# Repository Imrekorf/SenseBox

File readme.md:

# Table of contents
- [Table of contents](#table-of-contents)
- [setup guide](#setup-guide)
- [Hardware setup guide](#hardware-setup-guide)
	- [Soldering list](#soldering-list)
	- [Managing the power source](#managing-the-power-source)
	- [Connecting the sensors](#connecting-the-sensors)
		- [Datasheets from the currently used sensors](#datasheets-from-the-currently-used-sensors)
		- [Schematics usage](#schematics-usage)
- [Programming the PCB](#programming-the-pcb)
- [Troubleshooting errors](#troubleshooting-errors)
	- [RTC](#rtc)
	- [SD](#sd)
	- [Sensor initialisation errors](#sensor-initialisation-errors)
- [Correct Installation check](#correct-installation-check)

# setup guide

1. Clone this github repo
2. Generate a MQTTSettings.dat file using the ArduinoConfig-Generator script.
3. Move generated MQTTSettings.dat to SD card's root folder.
4. Power the PCB.

# Hardware setup guide

## Soldering list
1. Solder the DC barreljack
2. Solder the BT1 Battery holder.[^1]
3. Solder the Laser dust sensor connector pins.[^1]
4. Solder the VR5V and VR5V jumpers.

[^1]: Currently the Laser Dust sensor connectors and Battery holder have not yet arrived so that sensor and battery holder can not be connected yet.

## Managing the power source
Depending on the circumstance you might want to power the PCB from the USB connection.<br>
To do this, **first**, you must make sure that VR5V and VR3V3 solder pads are not soldered. This can be identified by seeing 2 small pads on both the solder pads.<br>
Secondly you must solder the USB3V3 and USB5V to provide power to the board from the USB.<br>
If the DC barreljack is used you must **desolder** the USB3V3 and USB5V and then solder the VR3V3 and VR5V.<br>
<br>
To power the RTC you must either solder on the battery holder on the BT1 footprint. Or you can solder a wire from the VR3V3 or USB3V3, whichever is currently providing the 3V3 power, to the 3V3 pad of the Battery holder pads. See the board schematic included in the Schematics folder for more details.<br><br>

## Connecting the sensors
The sensors should be connected to the different JST headers provided on the board. To do this you need male `JST-PH 2.0 4 pin connectors`. 
These can be ordered from [vanallesenmeer.nl](https://www.vanallesenmeer.nl/JST-2.0-PH-4pin-set-recht-met-kabel-30cm) for €0.95.
These cables' other end can then be soldered to the sensors. Currently i2c compatible devices are wired as followed from left to right:
1. SCL : black
2. SDA : red
3. 3v3 : white
4. GND : yellow.

Other sensors' connection diagrams should be taken from the provided schematics.

### Datasheets from the currently used sensors
- [SCD30-datasheet](https://docs.rs-online.com/2d49/0900766b816b6f9d.pdf) & [SCD30-interface descriptor](https://docs.rs-online.com/ba78/0900766b816b6f9c.pdf)
- [Ambimate datasheet](https://docs.rs-online.com/6304/A700000006497831.pdf), [Product specifications](https://www.te.com/commerce/DocumentDelivery/DDEController?Action=srchrtrv&DocNm=108-133092&DocType=SS&DocLang=EN), [Application Specifications](https://www.te.com/commerce/DocumentDelivery/DDEController?Action=showdoc&DocId=Specification+Or+Standard%7F114-133092%7FB%7Fpdf%7FEnglish%7FENG_SS_114-133092_B.pdf%7FN-A), [customer drawings](https://eu.mouser.com/datasheet/2/418/7/ENG_CD_2314291_A2-2032749.pdf)
- [TSL2591](https://learn.adafruit.com/adafruit-tsl2591/downloads)
- [AS7262](https://learn.adafruit.com/adafruit-as7262-6-channel-visible-light-sensor/overview)
- [SM-UART-04L](https://www.farnell.com/datasheets/2756490.pdf)
- [MIX8410](https://wiki.seeedstudio.com/Grove-Gas_Sensor-O2-MIX8410/)
- [MAX4466](https://datasheets.maximintegrated.com/en/ds/MAX4465-MAX4469.pdf)
- [PCF8563](https://www.nxp.com/docs/en/data-sheet/PCF8563.pdf)

Any other datasheets needed are included in the EAGLE library. Check the description of the different components to find these datasheets.

### Schematics usage
The .sch and .brd file contain the electrical diagrams and PCB board layout respectively. The pdf contains a quick summary of the .sch file.
The .sch and .brd files can be loaded into the Autocad EAGLE software to make changes and view other information.
The .csv files contain JLCPCB part numbers and placements. These are used to order the right SMD components on the board.

# Programming the PCB
To program the ESP32 on the PCB, provide a power source, either through the USB or the barrel jack depending on the currently soldered connections.
Then load the code into the arduino ide by opening the .ino file. You then need to select the ESP32 dev module as your board in the Tools section.
If this is not already present follow the following [tutorial](https://randomnerdtutorials.com/installing-the-esp32-board-in-arduino-ide-windows-instructions/) to add support for these boards.
Select the correct port in the arduino ide and upload the code.
**important:** when the "connecting ...." prompt comes up, press and hold the RST and BOOT buttons, then release the RST button. if the prompt stops printing `.` or `-`'s then release the BOOT button.

# Troubleshooting errors
The most common errors in the serial output will be that either the RTC, SD or other sensors are not connected. Currently the program does not stop at these errors which could lead to a SYS_RST error message from the ESP32.
## RTC
If the RTC is not working there is either a short circuit on the i2c bus or the RTC does not have power. The RTC is the first module to be initialized in the system for logging purposes, so this has some major consequences when it's not working.

## SD
The most common SD card error is that it is not plugged in. Which can be solved by plugging in the SD card, or replugging the SD card and restarting the system when it was plugged in.
The provided SD card should be flashed with an FAT32 format to make sure the ESP32 can write to it.

## Sensor initialisation errors
If problems arise with the sensors not initializing it is likely due to bad wiring or not being connected at all.

# Correct Installation check
If the installation and connections are all correct you should see the following popping up in the serial monitor after a reset.

```
[14:39:31] [Info]: AmbiMate Firmware version 2.8
[14:39:32] [Info]: AS7262 initialized
[14:39:32] [Info]: SM_UART_4L found and initialized.
[14:39:32] [Info]: SCD30 initialized.
[14:39:32] [Info]: Found a TSL2591 sensor
[14:39:32] [Info]: TSL2591 bootup
------------------------------------
Gain:         25x (Medium)
Timing:       300 ms
------------------------------------

[14:39:33] [Info]: Connecting to WiFi .......
Connencted to wiFi with ip: 192.168.178.53
[14:39:38] [Info]: 
Starting connection to server...
[14:39:38] [Info]: The client SenseBox_test connects to the public mqtt broker
[54:39:40] [Info]: Mqtt broker connected
```

Followed by Info logs containing sensor data.
This data should also be partially tracable to the IoT platform.

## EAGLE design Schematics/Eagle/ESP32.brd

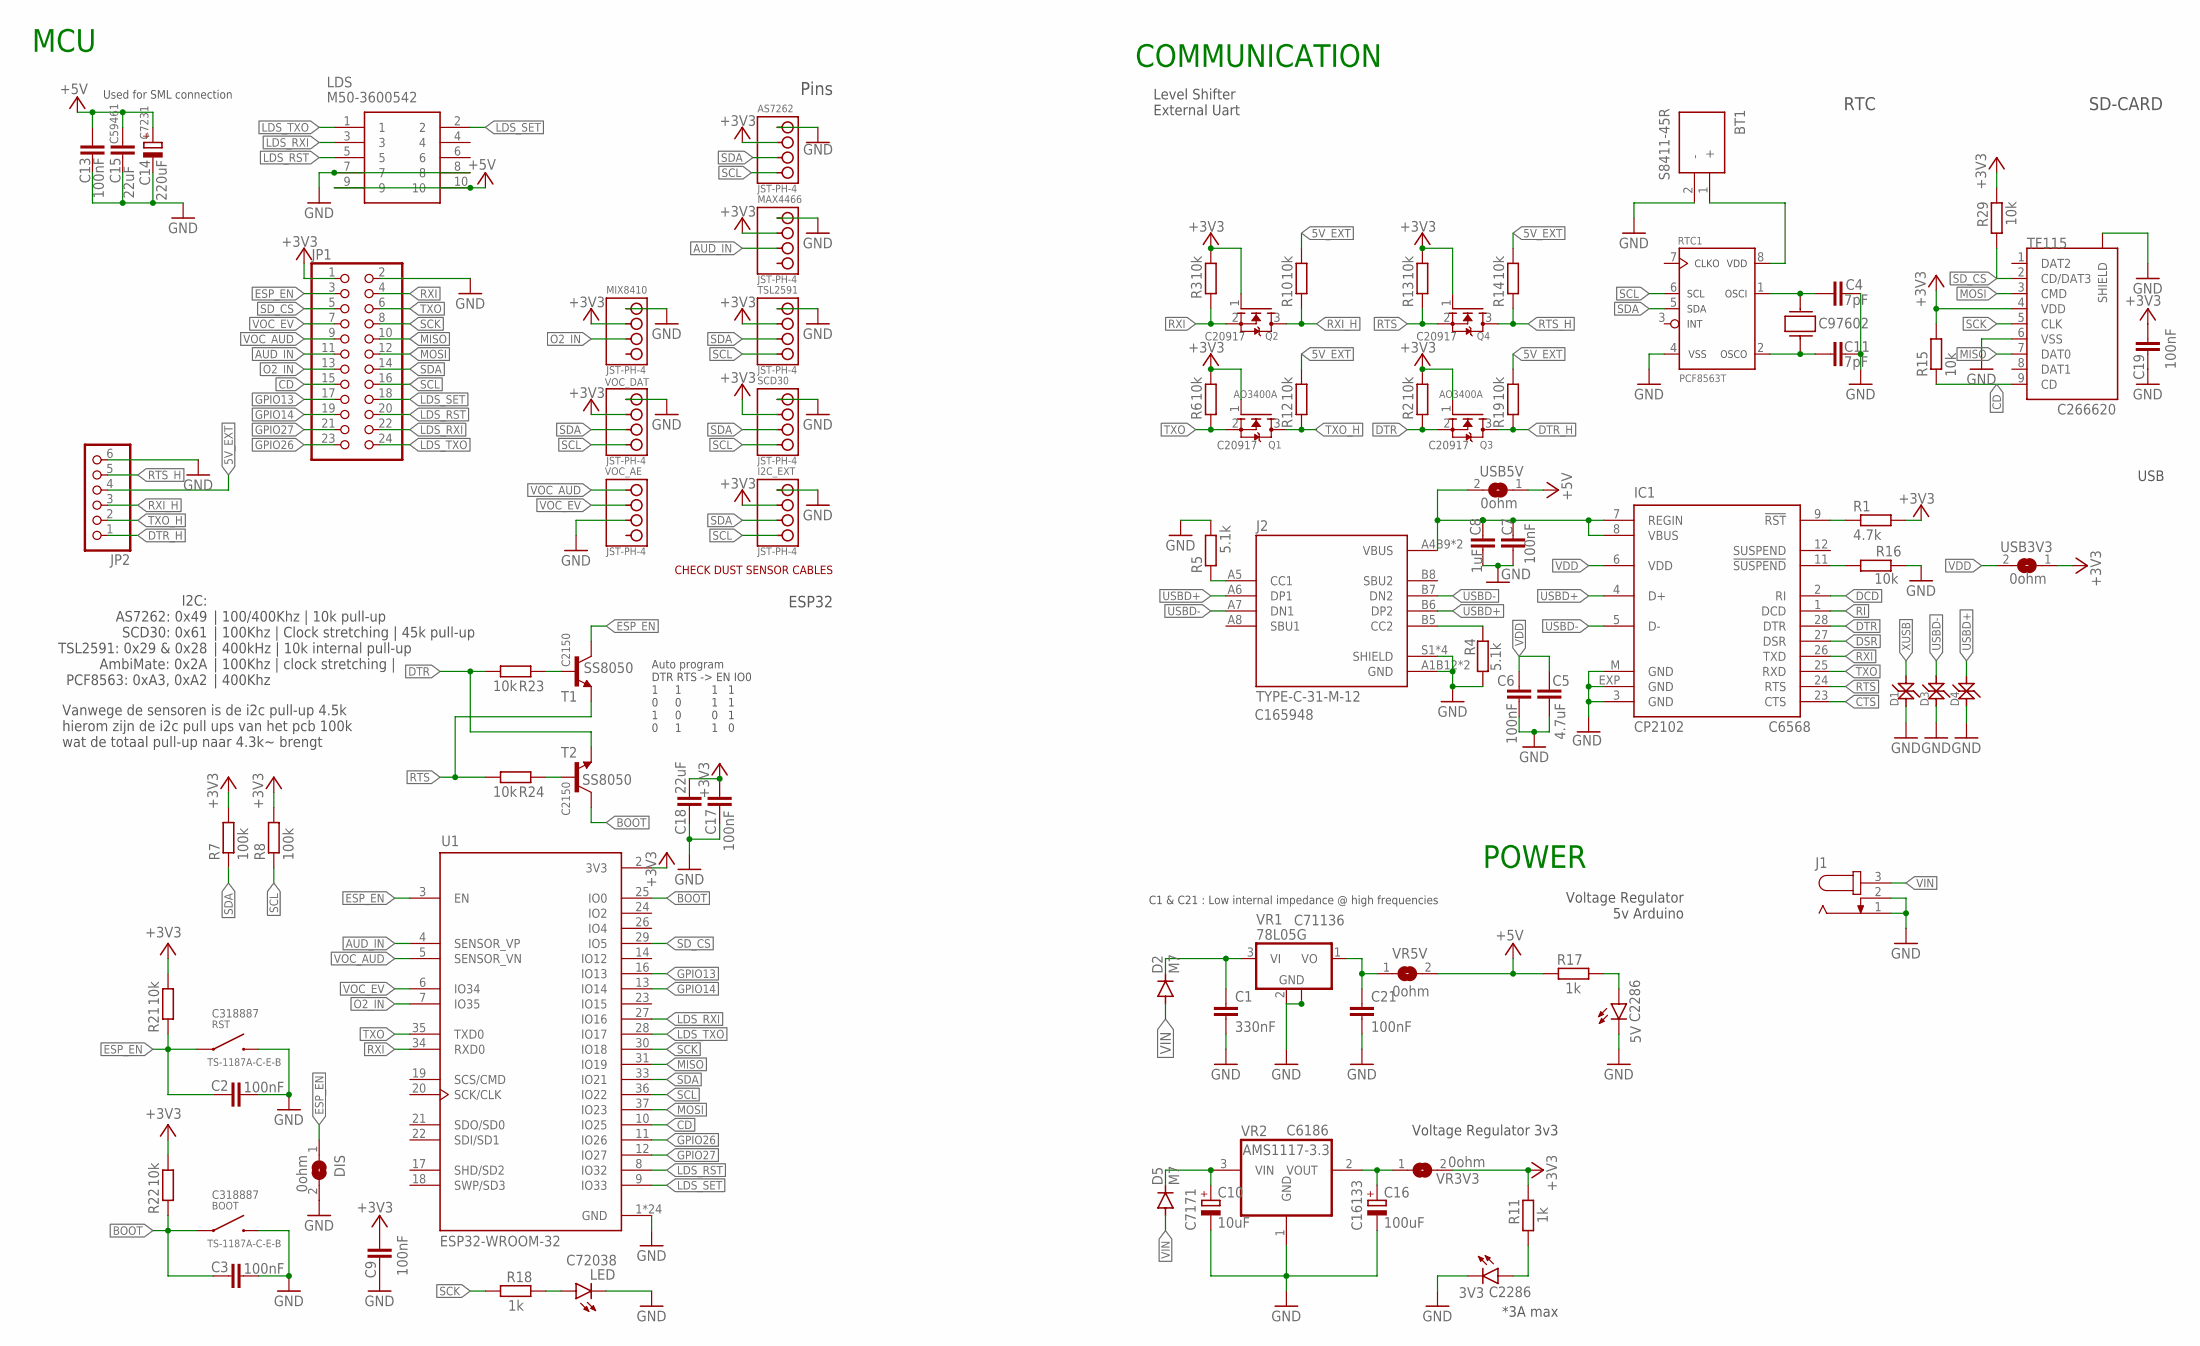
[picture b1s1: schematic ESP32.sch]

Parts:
3V3, 5V: C2286; CHIPLED_0603
AS7262: JST-PH-4
BOOT: TS-1187A-C-E-B
BT1: S8411-45R; S8411-45R_1
C1: 330nF; C0805
C2, C3, C6, C7, C9, C13, C17, C19, C21: 100nF; C0402
C4, C11: 7pF; C0402
C5: 4.7uF; C0402
C8: 1uF; C0402
C10: 10uF; A/3216-18R
C14: 220uF; D/7343-31R
C15, C18: 22uF; C0603
C16: 100uF; B/3528-21W
D1, D3, D4: LESD5D5.0CT1G
D2, D5: M7; DO-214AC
DIS: 0ohm; SJ
G1: 32.768KHZ
I2C_EXT: JST-PH-4
IC1: CP2102; MLP28
J1: JACK-PLUG1; SPC4078
J2: TYPE-C-31-M-12; HRO_TYPE-C-31-M-12
JP1: PINHD-2X12; 2X12
JP2: PINHD-1X6/90; 1X06/90
LDS: M50-3600542; M503600542
LED: YELLOW; CHIPLED_0603
MAX4466: JST-PH-4
MIX8410: JST-PH-4
Q1, Q2, Q3, Q4: AO3400A; SOT23
R1: 4.7k; R0402
R2, R3, R6, R10, R12, R13, R14, R15, R16, R19, R21, R22, R23, R24, R29: 10k; R0402
R4, R5: 5.1k; R0402
R7, R8: 100k; R0402
R11, R17, R18: 1k; R0805
RST: TS-1187A-C-E-B
RTC1: PCF8563T; SOIC8
SCD30: JST-PH-4
T1, T2: SS8050; SOT23-BEC
TF115: TF-115
TSL2591: JST-PH-4
U1: ESP32-WROOM-32; MODULE_ESP32-WROOM-32
USB3V3, USB5V: 0ohm; SJ
VOC_AE: JST-PH-4
VOC_DAT: JST-PH-4
VR1: 78L05G; SOT89
VR2: AMS1117-3.3; SOT223
VR3V3, VR5V: 0ohm; SJ

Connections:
5V_EXT: JP2.4, R10.1, R12.1, R14.1, R19.1
+3V3: AS7262.P2 (2), C9.2, C17.2, C18.2, C19.2, I2C_EXT.P2 (2), JP1.1, MAX4466.P2 (2), MIX8410.P2 (2), Q1.1 (G), Q2.1 (G), Q3.1 (G), Q4.1 (G), R1.2, R2.1, R3.1, R6.1, R7.2, R8.2, R11.2, R13.1, R15.2, R21.1, R22.1, R29.2, SCD30.P2 (2), TF115.4 (VDD), TSL2591.P2 (2), U1.2 (3V3), USB3V3.1, VOC_DAT.P2 (2), VR3V3.2
+5V: C13.1, C14.+, C15.1, LDS.9, LDS.10, R17.2, USB5V.1, VR5V.2
AUD_IN: JP1.11, MAX4466.P3 (3), U1.4 (SENSOR_VP)
BOOT: BOOT.A, BOOT.B (A), C3.1, R22.2, T2.C, U1.25 (IO0)
CD: JP1.15, R15.1, TF115.9 (CD), U1.10 (IO25)
CTS: IC1.23 (CTS)
DCD: IC1.2 (RI)
DSR: IC1.27 (DSR)
DTR: IC1.28 (DTR), Q3.2 (S), R2.2, R23.1, T2.E
DTR_H: JP2.1, Q3.3 (D), R19.2
ESP_EN: C2.1, DIS.1, JP1.3, R21.2, RST.A, RST.B (A), T1.C, U1.3 (EN)
GND: 3V3.C, 5V.C, AS7262.P1 (1), BOOT.C, BOOT.D (C), BT1.2 (-), C1.2, C2.2, C3.2, C4.2, C5.2, C6.2, C7.2, C8.2, C9.1, C10.-, C11.2, C13.2, C14.-, C15.2, C16.-, C17.1, C18.1, C19.1, C21.2, D1.P$1, D3.P$1, D4.P$1, DIS.2, I2C_EXT.P1 (1), IC1.3 (GND), IC1.EXP (GND), IC1.M (GND), J1.1, J1.2, J2.A1B12 (GND), J2.B1A12 (GND), J2.S1 (SHIELD), J2.S2 (SHIELD), J2.S3 (SHIELD), J2.S4 (SHIELD), JP1.2, JP2.6, LDS.7, LDS.8, LED.C, MAX4466.P1 (1), MIX8410.P1 (1), R4.2, R5.2, R16.1, RST.C, RST.D (C), RTC1.4 (VSS), SCD30.P1 (1), TF115.6 (VSS), TF115.10 (SHIELD), TF115.11 (SHIELD), TF115.12 (SHIELD), TF115.13 (SHIELD), TSL2591.P1 (1), U1.1 (GND), U1.15 (GND), U1.38 (GND), U1.39_1 (GND), U1.39_2 (GND), U1.39_3 (GND), U1.39_4 (GND), U1.39_5 (GND), U1.39_6 (GND), U1.39_7 (GND), U1.39_8 (GND), U1.39_9 (GND), U1.39_10 (GND), U1.39_11 (GND), U1.39_12 (GND), U1.39_13 (GND), U1.39_14 (GND), U1.39_15 (GND), U1.39_16 (GND), U1.39_17 (GND), U1.39_18 (GND), U1.39_19 (GND), U1.39_20 (GND), U1.39_21 (GND), VOC_AE.P3 (3), VOC_DAT.P1 (1), VR1.2 (GND), VR1.2@1 (GND), VR2.1 (GND)
GPIO13: JP1.17, U1.16 (IO13)
GPIO14: JP1.19, U1.13 (IO14)
GPIO26: JP1.23, U1.11 (IO26)
GPIO27: JP1.21, U1.12 (IO27)
LDS_RST: JP1.20, LDS.5, U1.8 (IO32)
LDS_RXI: JP1.22, LDS.3, U1.27 (IO16)
LDS_SET: JP1.18, LDS.2, U1.9 (IO33)
LDS_TXO: JP1.24, LDS.1, U1.28 (IO17)
MISO: JP1.10, TF115.7 (DAT0), U1.31 (IO19)
MOSI: JP1.12, TF115.3 (CMD), U1.37 (IO23)
unnamed: C4.1, G1.2, RTC1.1 (OSCI)
unnamed: R23.2, T1.B
unnamed: BT1.1 (+), RTC1.8 (VDD)
unnamed: 3V3.A, R11.1
unnamed: IC1.9 (!RST), R1.1
unnamed: C11.1, G1.1, RTC1.2 (OSCO)
unnamed: C1.1, D2.C, VR1.3 (VI)
unnamed: LED.A, R18.2
unnamed: R24.2, T2.B
unnamed: J2.B5 (CC2), R4.1
unnamed: J2.A5 (CC1), R5.1
unnamed: IC1.11 (!SUSPEND), R16.2
unnamed: C21.1, VR1.1 (VO), VR5V.1
unnamed: C16.+, VR2.2 (VOUT), VR3V3.1
unnamed: 5V.A, R17.1
unnamed: C10.+, D5.C, VR2.3 (VIN)
O2_IN: JP1.13, MIX8410.P3 (3), U1.7 (IO35)
RI: IC1.1 (DCD)
RTS: IC1.24 (RTS), Q4.2 (S), R13.2, R24.1, T1.E
RTS_H: JP2.5, Q4.3 (D), R14.2
RXI: IC1.26 (TXD), JP1.4, Q2.2 (S), R3.2, U1.34 (RXD0)
RXI_H: JP2.3, Q2.3 (D), R10.2
SCK: JP1.8, R18.1, TF115.5 (CLK), U1.30 (IO18)
SCL: AS7262.P4 (4), I2C_EXT.P4 (4), JP1.16, R8.1, RTC1.6 (SCL), SCD30.P4 (4), TSL2591.P4 (4), U1.36 (IO22), VOC_DAT.P4 (4)
SDA: AS7262.P3 (3), I2C_EXT.P3 (3), JP1.14, R7.1, RTC1.5 (SDA), SCD30.P3 (3), TSL2591.P3 (3), U1.33 (IO21), VOC_DAT.P3 (3)
SD_CS: JP1.5, R29.1, TF115.2 (CD/DAT3), U1.29 (IO5)
TXO: IC1.25 (RXD), JP1.6, Q1.2 (S), R6.2, U1.35 (TXD0)
TXO_H: JP2.2, Q1.3 (D), R12.2
USBD+: D4.P$2, IC1.4 (D+), J2.A6 (DP1), J2.B6 (DP2)
USBD-: D3.P$2, IC1.5 (D-), J2.A7 (DN1), J2.B7 (DN2)
VDD: C5.1, C6.1, IC1.6 (VDD), USB3V3.2
VIN: D2.A, D5.A, J1.3
VOC_AUD: JP1.9, U1.5 (SENSOR_VN), VOC_AE.P1 (1)
VOC_EV: JP1.7, U1.6 (IO34), VOC_AE.P2 (2)
XUSB: C7.1, C8.1, D1.P$2, IC1.7 (REGIN), IC1.8 (VBUS), J2.A4B9 (VBUS), J2.B4A9 (VBUS), USB5V.2

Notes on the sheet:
USB
Pins
Voltage Regulator 3v3
*3A max
Voltage Regulator 5v Arduino
POWER
COMMUNICATION
MCU
CHECK DUST SENSOR CABLES
RTC
SD-CARD
I2C: AS7262: 0x49 SCD30: 0x61 TSL2591: 0x29 & 0x28 AmbiMate: 0x2A PCF8563: 0xA3, 0xA2
C1 & C21 : Low internal impedance @ high frequencies
Used for SML connection
| 100/400Khz | 10k pull-up | 100Khz | Clock stretching | 45k pull-up | 400kHz | 10k internal pull-up | 100Khz | clock stretching | | 400Khz
Auto program DTR RTS -> EN IO0 1 1 1 1 0 0 1 1 1 0 0 1 0 1 1 0
Level Shifter External Uart
ESP32
Vanwege de sensoren is de i2c pull-up 4.5k hierom zijn de i2c pull ups van het pcb 100k wat de totaal pull-up naar 4.3k~ brengt

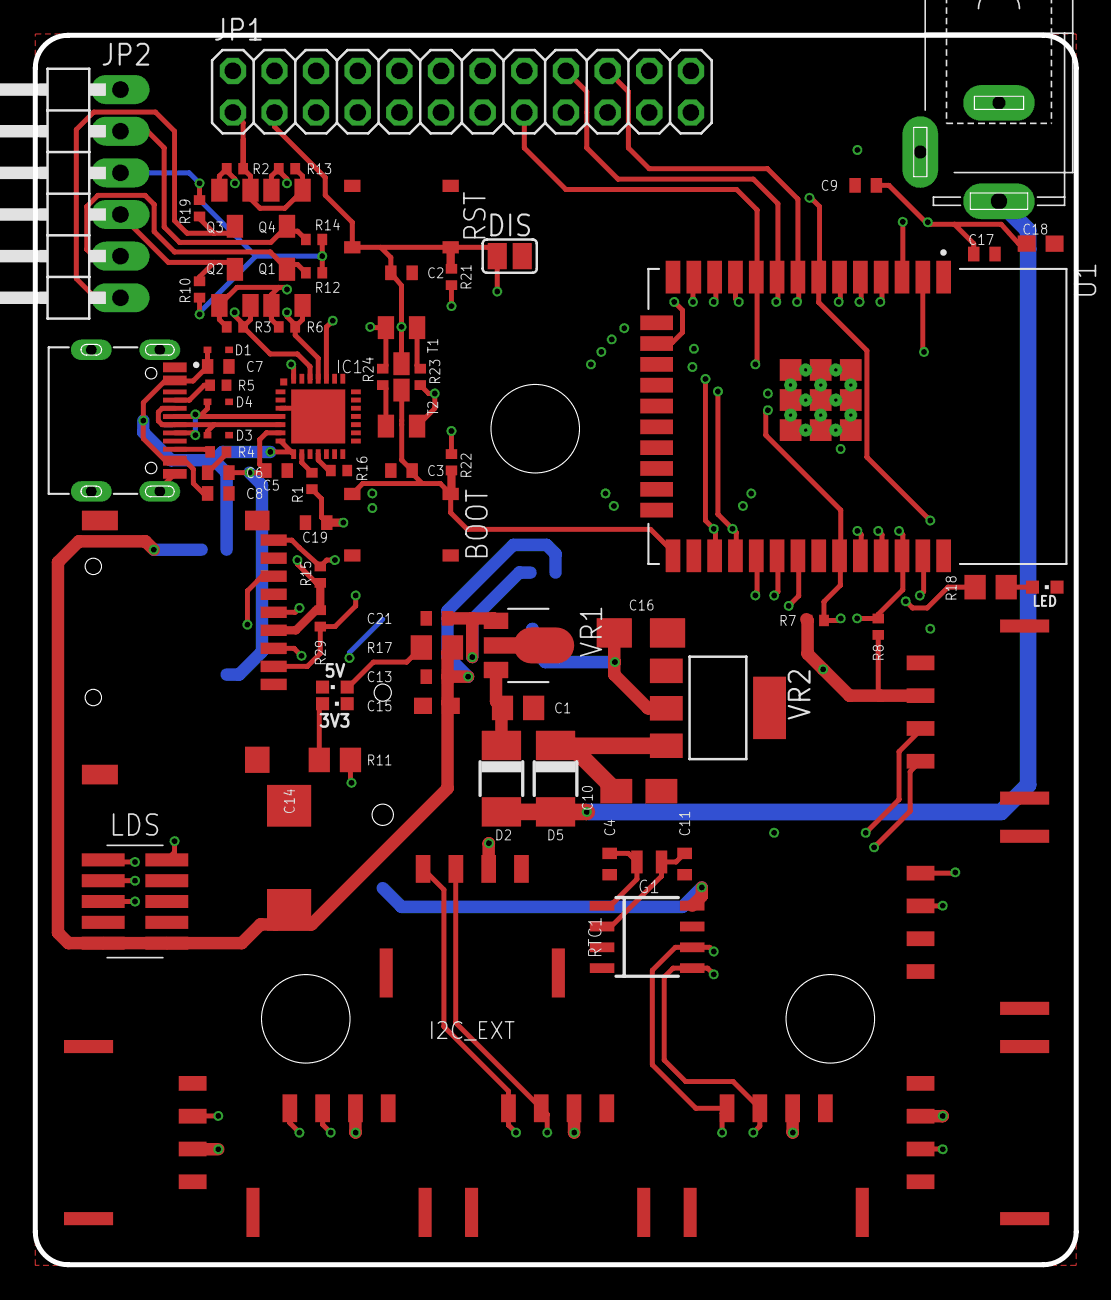
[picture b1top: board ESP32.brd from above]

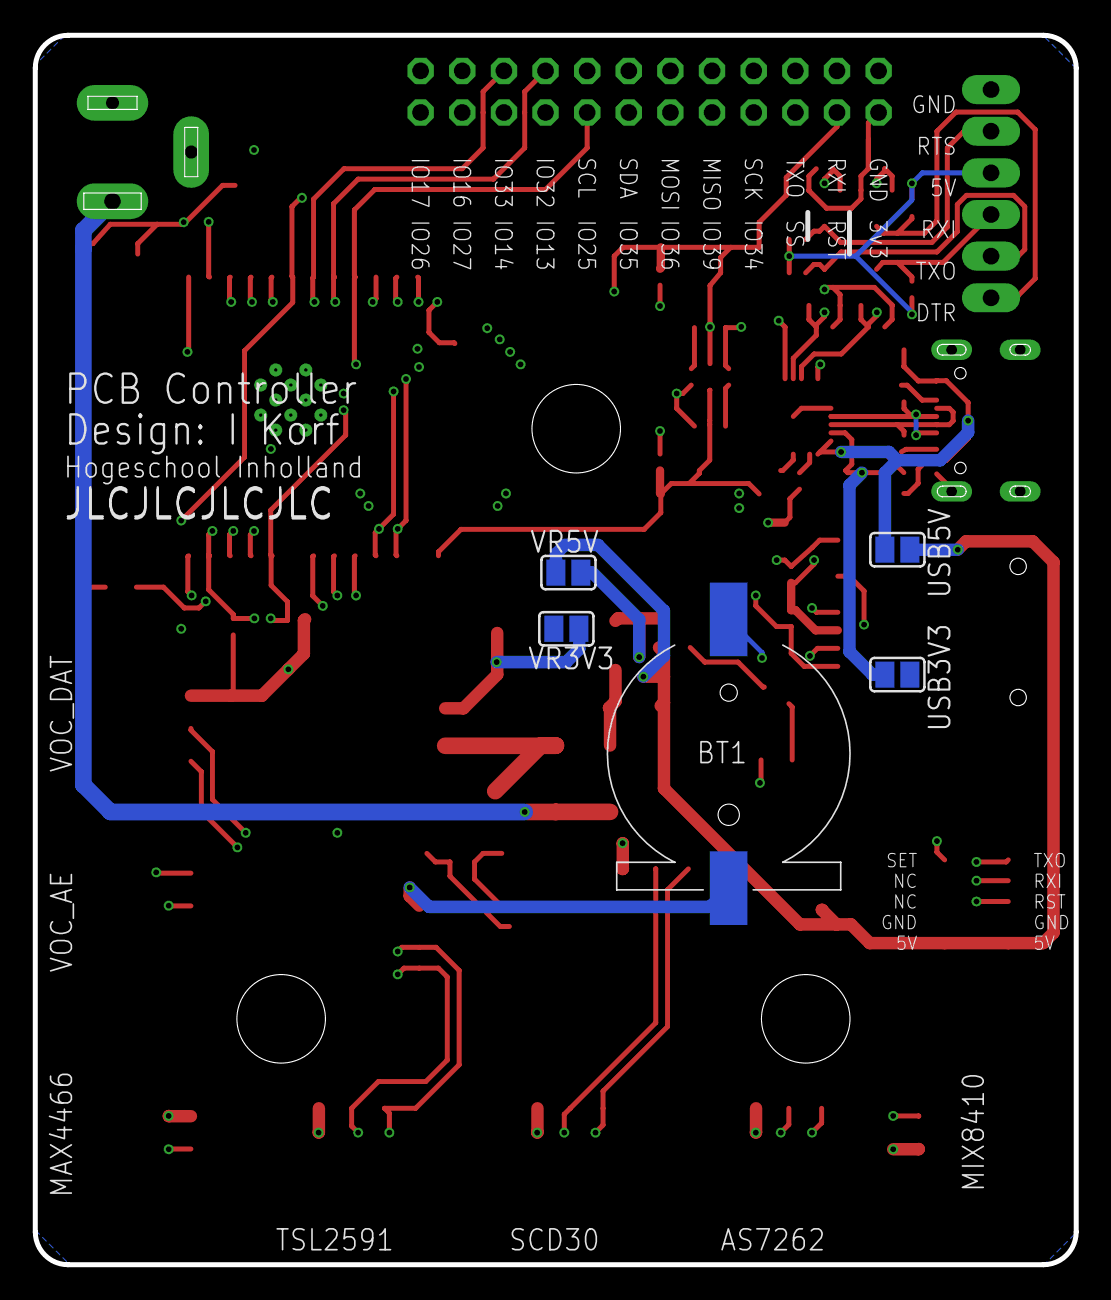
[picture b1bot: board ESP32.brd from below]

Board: 4 copper layers, 63.5 x 75.0 mm, 84 parts (5 on the bottom side), 54 nets.
